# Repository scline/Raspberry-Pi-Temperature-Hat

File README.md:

# Raspberry-Pi Temperature Sensor Hat
This repo is to track and update the progress of a custom PCB application to use with the Raspberry Pi system. The purpose is to attach multiple temperature sensors to create a wi-fi based monitor.

## Change Log
v1.0 - Initial board release for Raspberry Pi 2 / A+ models

## Software Used
To create the board I used the free version of [Eagle](http://www.cadsoftusa.com/eagle-pcb-design-software/about-eagle/). All you need to do is import the folder to load and start editing.

## Ordering PCB
There are many services that can create and print this board for you, I used [oshpark](https://oshpark.com/) due to ease of use and cheap processing. It was ~$30 to print this board (you get 3 of them whith your order) so it came out to about $10 each. You can get a 3D version of this board by using [EagleUP](https://eagleup.wordpress.com/installation-and-setup/)

## Parts 
The following parts are requred to complete this board. Links are just used as examples - ebay and other sites likely have these parts cheaper if you can wait for shipping.
* 1x [GPIO Header for Raspberry Pi A+/B+/Pi 2 - 2x20 Female Header](https://www.adafruit.com/products/2222)
* 3x [USB-A Jack*](https://www.adafruit.com/products/2225) 
* 3x [USB-A Connector*](https://www.adafruit.com/products/1387) 
* 3x [Dallas DS18B20 Sensors*](http://www.amazon.com/gp/product/B00CHEZ250?keywords=DS18B20&qid=1451202686&ref_=sr_1_1&sr=8-1)
* 1x [4.7k Resisitor*](https://www.adafruit.com/products/2783)
* 1x [DHT22 Sensor](http://www.amazon.com/SMAKN%C2%AE-Digital-Temperature-Humidity-Measurement/dp/B00MIBRFTI/ref=sr_1_1?ie=UTF8&qid=1451202874&sr=8-1&keywords=DHT22)
* 1x [10k Resistor](https://www.adafruit.com/products/2784) 

*You may need less depending on how manny sensor cords you want, if you only need 1 sensor then you can get away with just the 10k resistor + DHT22 sensor5

## Printed Circuit Board v1.0
Below is the 2D versions of this board rendered by Eagle software.

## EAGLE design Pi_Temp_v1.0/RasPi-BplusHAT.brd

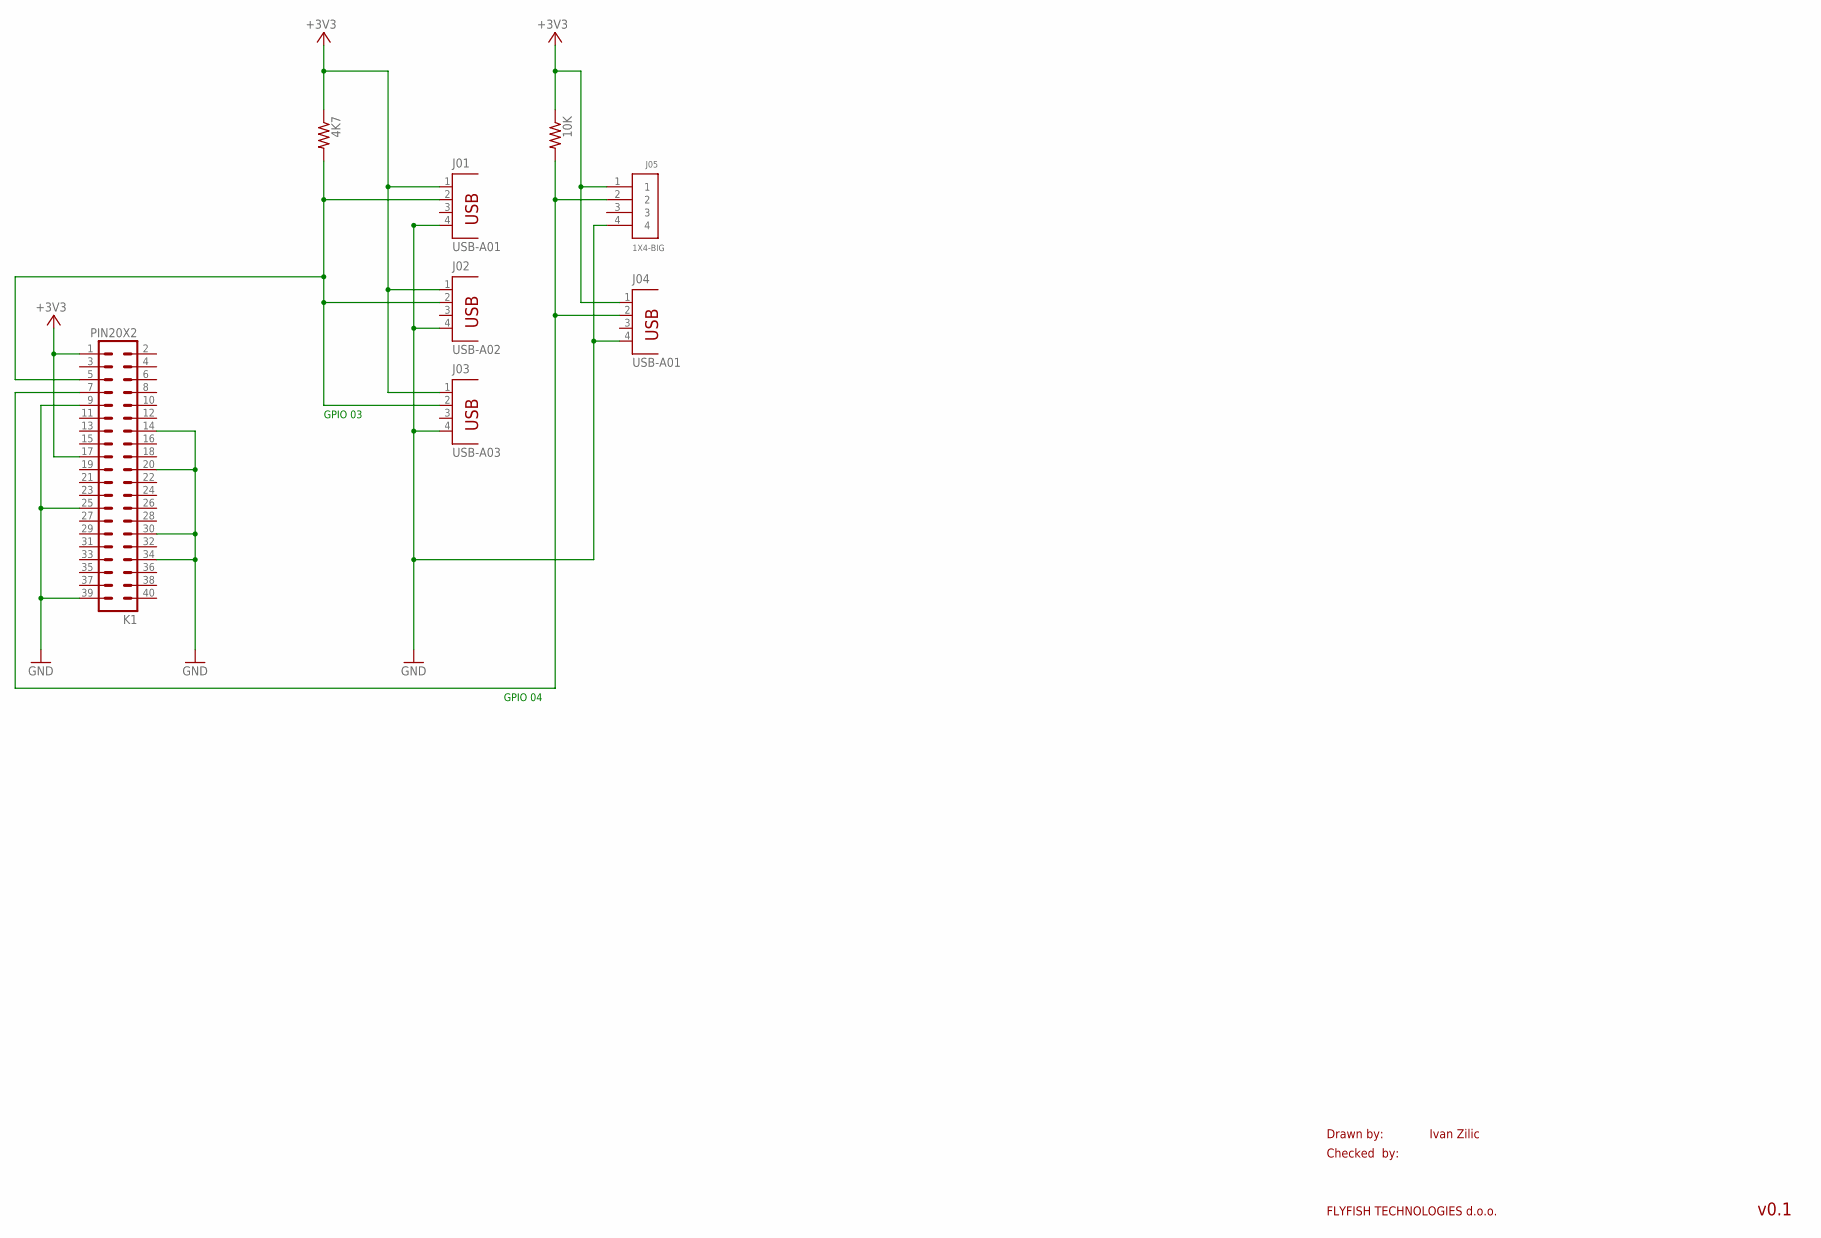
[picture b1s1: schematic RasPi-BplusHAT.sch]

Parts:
4K7, 10K: R-US_0204/7; 0204/7
J01, J04: USB-A01; PN87520
J02: USB-A02; PN87520
J03: USB-A03; PN87520
J05: 1X4-BIG; 1X04-BIG
K1: PIN20X2; PIN_20X2

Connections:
+3V3: 4K7.1, 10K.1, J01.1, J02.1, J03.1, J04.1, J05.1, K1.1, K1.17
GND: J01.4, J02.4, J03.4, J04.4, J05.4, K1.9, K1.14, K1.20, K1.25, K1.30, K1.34, K1.39
unnamed: 10K.2, J04.2, J05.2, K1.7
TMP01: 4K7.2, J01.2, J02.2, J03.2, K1.5

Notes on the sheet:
Drawn by:
Checked by:
FLYFISH TECHNOLOGIES d.o.o.
Ivan Zilic
v0.1
GPIO 03
GPIO 04

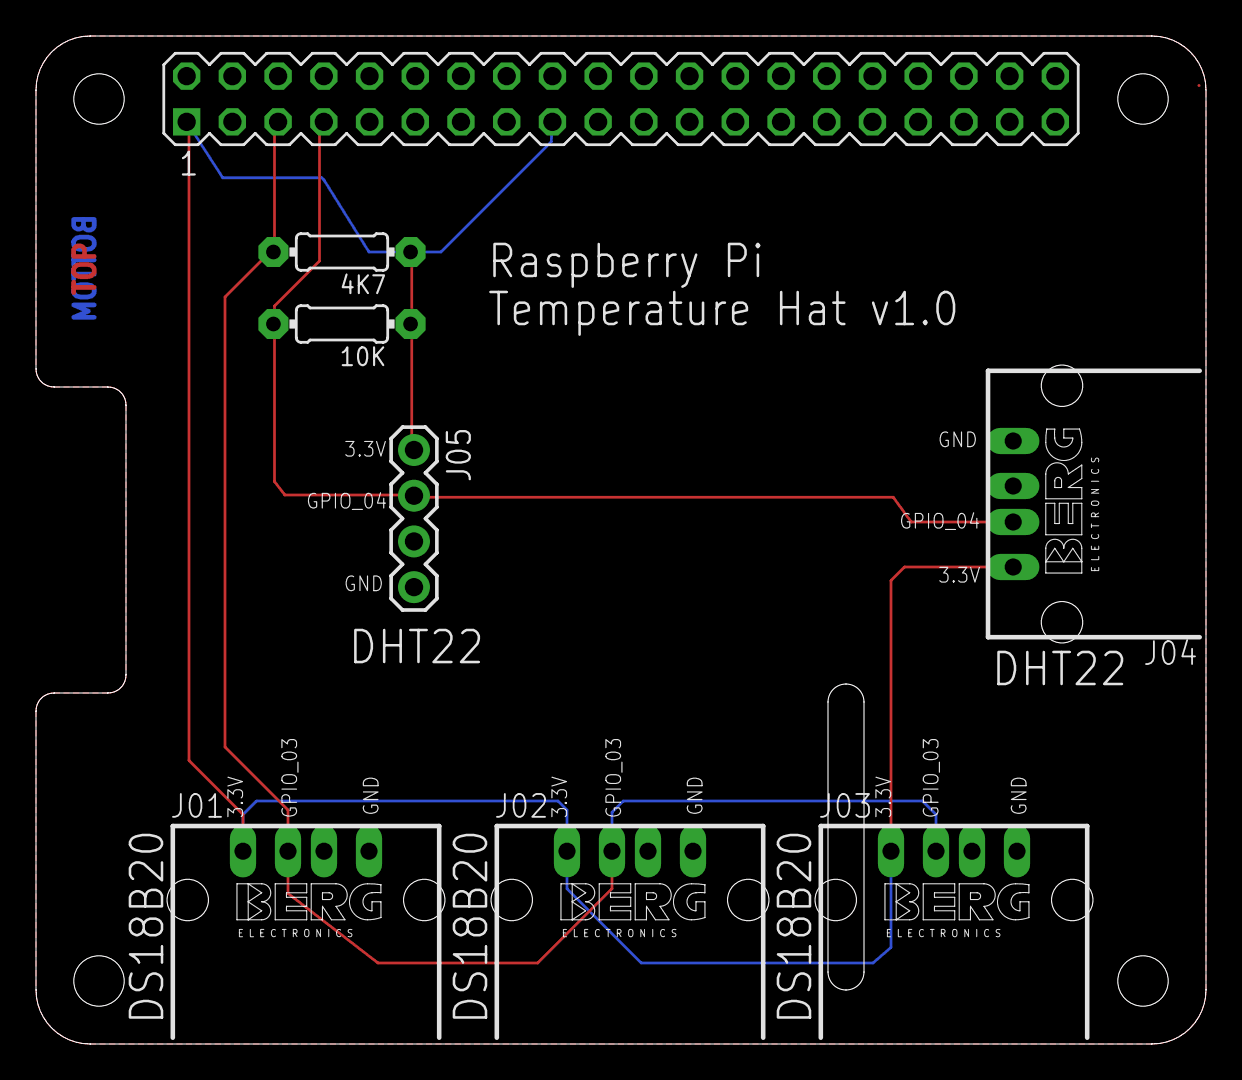
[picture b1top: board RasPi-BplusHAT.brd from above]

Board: 2 copper layers, 65.0 x 56.0 mm, 8 parts (0 on the bottom side), 4 nets.

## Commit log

2015-12-27 Initial Push
2015-12-27 v1.0 PCB
2015-12-27 Adding pictures
2015-12-27 Picture correction
2015-12-27 ReadMe Update
